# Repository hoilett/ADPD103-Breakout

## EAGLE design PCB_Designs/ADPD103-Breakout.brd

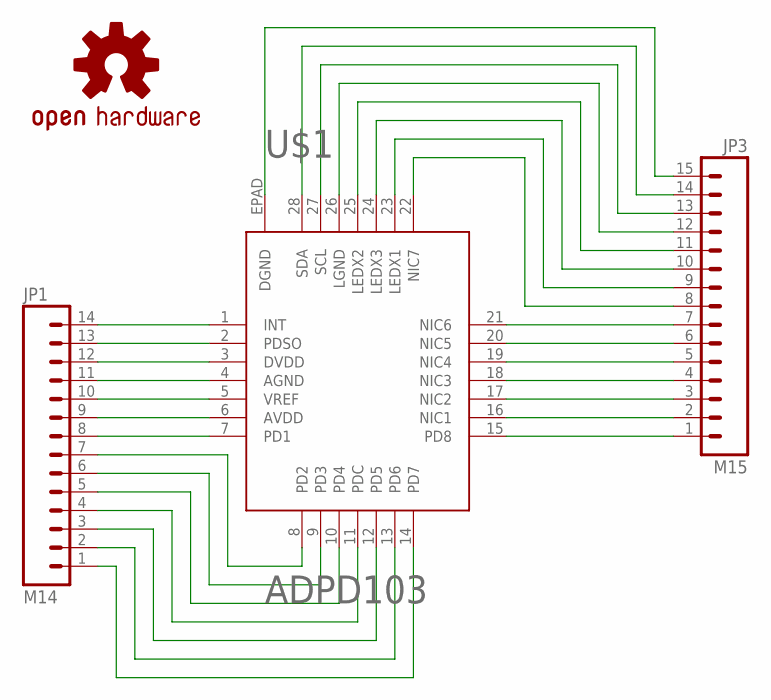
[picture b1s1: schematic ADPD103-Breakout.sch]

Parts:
JP1: M14; 1X14
JP3: M15; 1X15
LOGO1: OSHW-LOGOS; OSHW-LOGO-S
U$1: ADPD103; 28-LFCSP

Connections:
unnamed: JP1.14, U$1.1 (INT)
unnamed: JP1.13, U$1.2 (PDSO)
unnamed: JP1.12, U$1.3 (DVDD)
unnamed: JP1.11, U$1.4 (AGND)
unnamed: JP1.10, U$1.5 (VREF)
unnamed: JP1.9, U$1.6 (AVDD)
unnamed: JP1.8, U$1.7 (PD1)
unnamed: JP1.7, U$1.8 (PD2)
unnamed: JP1.6, U$1.9 (PD3)
unnamed: JP1.5, U$1.10 (PD4)
unnamed: JP1.4, U$1.11 (PDC)
unnamed: JP1.3, U$1.12 (PD5)
unnamed: JP1.2, U$1.13 (PD6)
unnamed: JP1.1, U$1.14 (PD7)
unnamed: JP3.1, U$1.15 (PD8)
unnamed: JP3.2, U$1.16 (NIC1)
unnamed: JP3.3, U$1.17 (NIC2)
unnamed: JP3.4, U$1.18 (NIC3)
unnamed: JP3.5, U$1.19 (NIC4)
unnamed: JP3.6, U$1.20 (NIC5)
unnamed: JP3.7, U$1.21 (NIC6)
unnamed: JP3.8, U$1.22 (NIC7)
unnamed: JP3.15, U$1.EPAD (DGND)
unnamed: JP3.14, U$1.28 (SDA)
unnamed: JP3.13, U$1.27 (SCL)
unnamed: JP3.12, U$1.26 (LGND)
unnamed: JP3.11, U$1.25 (LEDX2)
unnamed: JP3.10, U$1.24 (LEDX3)
unnamed: JP3.9, U$1.23 (LEDX1)

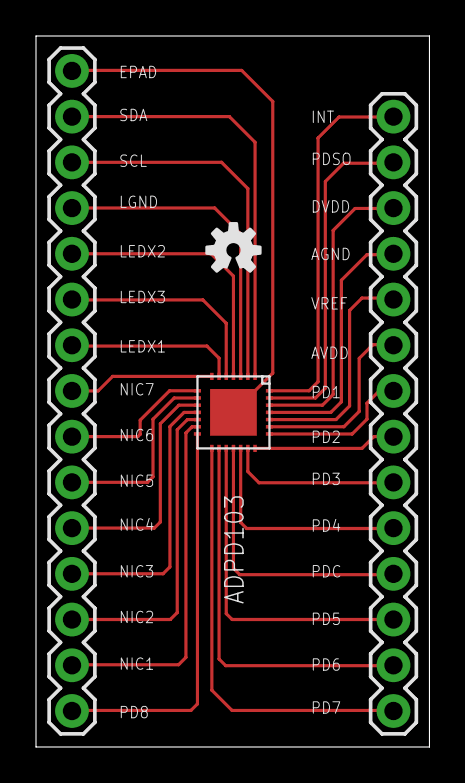
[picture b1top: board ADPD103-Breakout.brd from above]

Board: 2 copper layers, 21.9 x 39.5 mm, 4 parts (0 on the bottom side), 29 nets.

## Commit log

2016-07-15 initial file
2016-07-16 first order sent to OSHPark
2016-07-16 small change to sch file. just reorganized a single label

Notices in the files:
PCB_Designs/ADPD103-Breakout.sch:
Creative Commons License
parts and their libraries:
SparkFun-Connectors: Licensing: Creative Commons ShareAlike 4.0 International - https://creativecommons.org/licenses/by-sa/4.0
